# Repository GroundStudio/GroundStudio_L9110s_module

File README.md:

GroundStudio L9110s Dual Motor Driver Module
====================================

Get it from [ardushop.ro](https://ardushop.ro/ro/home/2525-modl9110s.html)

Explore all the GroundStudio products at [GroundStudio.ro](https://groundstudio.ro/)

Description
-------------------
Dual motor driver module based on two L9110S chips.

Contents
-------------------

* [/Documentation](https://github.com/GroundStudio/GroundStudio_L9110s_module/tree/main/Documentation) -- Contains documentation written during creation of this repository, with readme.md index of its own!
* [/Firmware](https://github.com/GroundStudio/GroundStudio_L9110s_module/tree/main/Firmware) -- Firmware (bootloaders, etc)
* [/Hardware](https://github.com/GroundStudio/GroundStudio_L9110s_module/tree/main/Hardware) -- Schematics, layout.
* [/Libraries](https://github.com/GroundStudio/GroundStudio_L9110s_module/tree/main/Libraries) -- Arduino/CircuitPython libraries. 
* [/Tools](https://github.com/GroundStudio/GroundStudio_L9110s_module/tree/main) -- Tools needed for compiling, uploading bootloader, etc.

Versions
-------------------
*(Not all tags shown)*
* [V0.0.2] Initial version

License
-------------------

This is released under the [Attribution-ShareAlike 4.0 International (CC BY-SA 4.0)](https://creativecommons.org/licenses/by-sa/4.0/) license. 
**You are welcome to use this for commercial purposes.**

Please consider contributing back to this project or others to help the open-source hardware community continue to thrive and grow! 

Certifications:

[Open Source Hardware Association](https://certification.oshwa.org/ro000014.html)   
   
[
](https://certification.oshwa.org/ro000014.html)

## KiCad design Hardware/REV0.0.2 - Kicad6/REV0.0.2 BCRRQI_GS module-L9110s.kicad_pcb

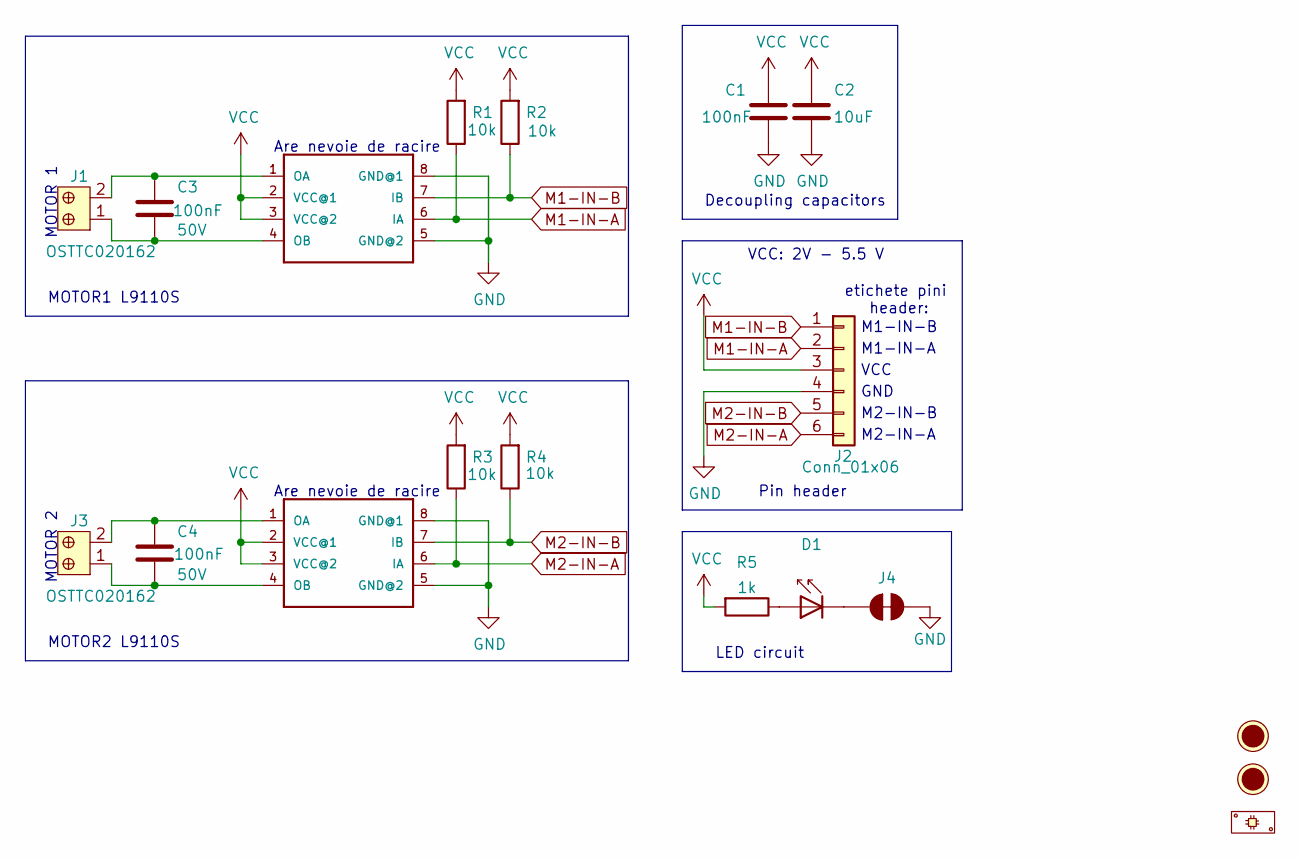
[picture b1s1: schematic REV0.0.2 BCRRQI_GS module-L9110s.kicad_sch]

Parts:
C1, C3, C4: C_0603_100nF_50V; C_0603; Rated voltage 50V; MPN TCC0603X7R104K500CT; LCSC C282519
C2: C_1206_10uF_25V; C_1206; Rated voltage 25V; MPN CL31B106KAHNNNE; LCSC C14860
D1: LED_0402_RED; LED_0402; MPN TZ-P2-0402RTIA1-0.45T; LCSC C779449
FID1, FID2: Fiducial; Fiducial_0.75mm_Mask1.5mm
J1, J3: OSTTC020162; WJ126V-5.0-2P; MPN WJ126V-5.0-2P; LCSC C8404
J2: Conn_01x06; PinHeader_1x06_P2.54mm_Vertical_Male; MPN C37208; LCSC C37208
J4: PWR LED DISABLE; SolderJumper_NC
P1: PCB; MPN BCRRQI_GS_PCB
R1, R2, R3, R4: R_0402_10k; R_0402; MPN 0402WGJ0103TCE; LCSC C25531
R5: R_0402_1k; R_0402; MPN RC-02W1001FT; LCSC C226166
U1, U2: L9110; SOIC-8_3.9x4.9mm_P1.27mm; MPN L9110S; LCSC C85174

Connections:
GND: C1.1, C2.2, J2.4, J4.1, U1.5 (GND@2), U1.8 (GND@1), U2.5 (GND@2), U2.8 (GND@1)
M1-IN-A: J2.2, R1.1, U1.6 (IA)
M1-IN-B: J2.1, R2.1, U1.7 (IB)
M2-IN-A: J2.6, R3.1, U2.6 (IA)
M2-IN-B: J2.5, R4.1, U2.7 (IB)
unnamed: C3.1, J1.2, U1.1 (OA)
unnamed: C3.2, J1.1, U1.4 (OB)
unnamed: C4.1, J3.2, U2.1 (OA)
unnamed: C4.2, J3.1, U2.4 (OB)
unnamed: D1.1 (K), J4.2
unnamed: D1.2 (A), R5.1
VCC: C1.2, C2.1, J2.3, R1.2, R2.2, R3.2, R4.2, R5.2, U1.2 (VCC@1), U1.3 (VCC@2), U2.2 (VCC@1), U2.3 (VCC@2)

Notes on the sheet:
VCC
MOTOR2 L9110S
Are nevoie de racire
Decoupling capacitors
M1-IN-B
GND
VCC: 2V - 5.5 V
M2-IN-B
MOTOR1 L9110S
LED circuit
M1-IN-A
MOTOR 1
M2-IN-A
MOTOR 2
Pin header
etichete pini header:

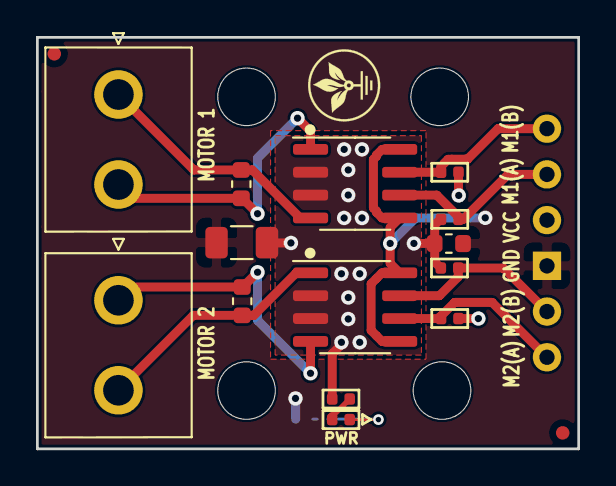
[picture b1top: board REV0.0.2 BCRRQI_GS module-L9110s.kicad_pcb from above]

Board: 2 copper layers, 30.1 x 22.9 mm, 18 parts (1 on the bottom side), 12 nets.

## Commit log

2023-10-23 - first commit
2023-11-03 - added datasheet
